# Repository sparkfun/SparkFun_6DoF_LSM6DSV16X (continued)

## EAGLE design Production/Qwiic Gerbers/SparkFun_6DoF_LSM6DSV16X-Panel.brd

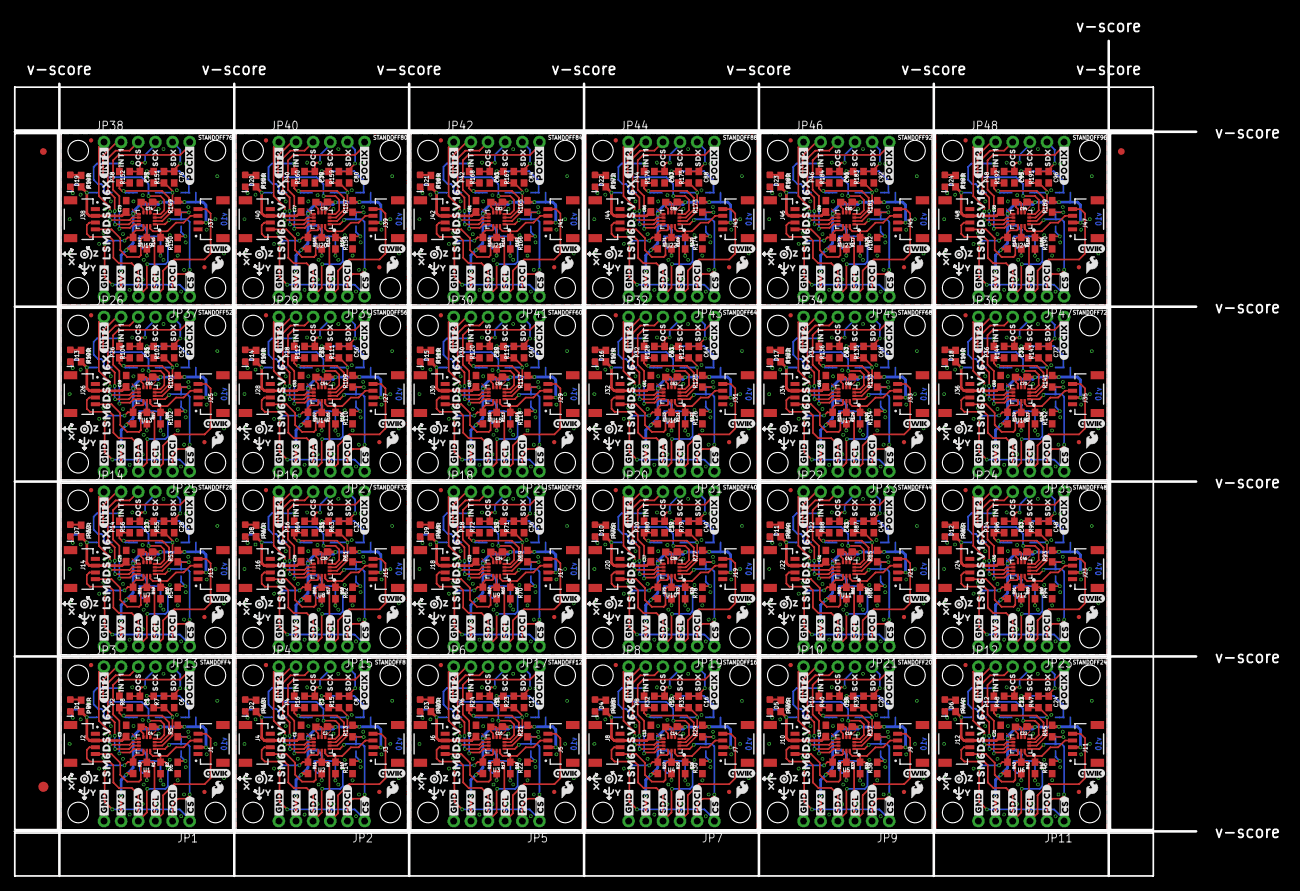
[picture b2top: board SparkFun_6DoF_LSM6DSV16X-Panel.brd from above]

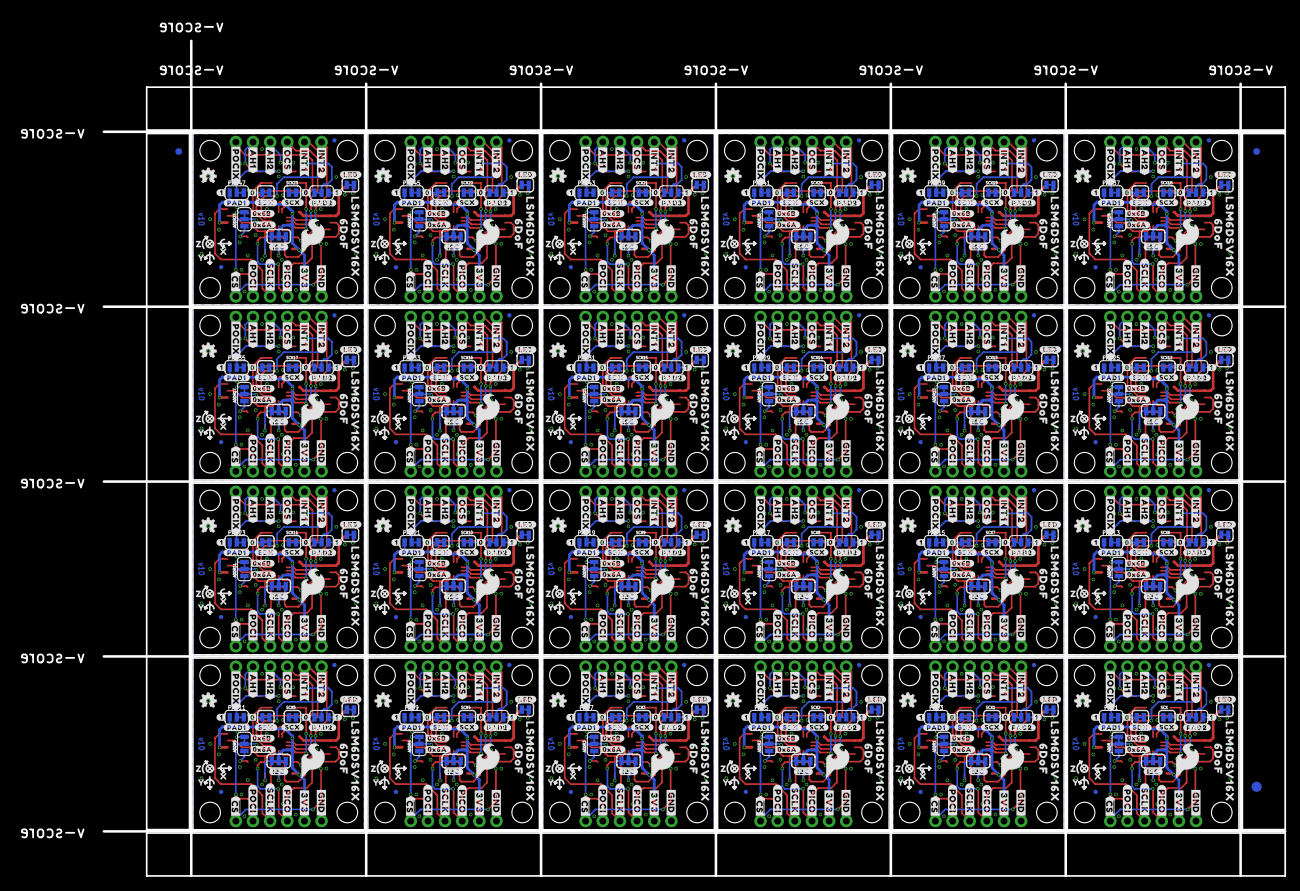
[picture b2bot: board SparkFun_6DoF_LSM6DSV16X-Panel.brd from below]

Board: 2 copper layers, 175.0 x 123.7 mm, 2094 parts (963 on the bottom side), 528 nets.

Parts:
ADDR, ADDR1, ADDR2, ADDR3, ADDR4, ADDR5, ADDR6, ADDR7, ADDR8, ADDR9, ADDR10, ADDR11, ADDR12, ADDR13, ADDR14, ADDR15, ADDR16, ADDR17, ADDR18, ADDR19, ADDR20, ADDR21, ADDR22, ADDR23: JUMPER-SMT_3_1-NC_TRACE_SILK; SMT-JUMPER_3_1-NC_TRACE_SILK
C1, C2, C3, C4, C9, C10, C13, C14, C17, C18, C21, C22, C25, C26, C29, C30, C33, C34, C37, C38, C41, C42, C45, C46, C49, C50, C53, C54, C57, C58, C61, C62, C65, C66, C69, C70, C73, C74, C77, C78, C81, C82, C85, C86, C89, C90, C93, C94: 0.1uF; 0603
C5, C6, C7, C8, C11, C12, C15, C16, C19, C20, C23, C24, C27, C28, C31, C32, C35, C36, C39, C40, C43, C44, C47, C48, C51, C52, C55, C56, C59, C60, C63, C64, C67, C68, C71, C72, C75, C76, C79, C80, C83, C84, C87, C88, C91, C92, C95, C96: 110pF; 0603
D1, D2, D3, D4, D5, D6, D7, D8, D9, D10, D11, D12, D13, D14, D15, D16, D17, D18, D19, D20, D21, D22, D23, D24: RED; LED-0603
E$1, E$2, E$3, E$4: FIDUCIAL-1X2
E$5, E$6: FIDUCIAL-1.5X3
FD1, FD2, FD3, FD4, FD5, FD6, FD7, FD8, FD9, FD10, FD11, FD12, FD13, FD14, FD15, FD16, FD17, FD18, FD19, FD20, FD21, FD22, FD23, FD24, FD25, FD26, FD27, FD28, FD29, FD30, FD31, FD32, FD33, FD34, FD35, FD36, FD37, FD38, FD39, FD40, FD41, FD42, FD43, FD44, FD45, FD46, FD47, FD48: FIDUCIALUFIDUCIAL; FIDUCIAL-MICRO
FID1, FID2, FID3, FID4, FID5, FID6, FID7, FID8, FID9, FID10, FID11, FID12, FID13, FID14, FID15, FID16, FID17, FID18, FID19, FID20, FID21, FID22, FID23, FID24, FID25, FID26, FID27, FID28, FID29, FID30, FID31, FID32, FID33, FID34, FID35, FID36, FID37, FID38, FID39, FID40, FID41, FID42, FID43, FID44, FID45, FID46, FID47, FID48: FIDUCIALUFIDUCIAL; FIDUCIAL-MICRO
FRAME1, FRAME2, FRAME3, FRAME4, FRAME5, FRAME6, FRAME7, FRAME8, FRAME9, FRAME10, FRAME11, FRAME12, FRAME13, FRAME14, FRAME15, FRAME16, FRAME17, FRAME18, FRAME19, FRAME20, FRAME21, FRAME22, FRAME23, FRAME24: FRAME-LEDGER; CREATIVE_COMMONS
I2C_PU, I2C_PU1, I2C_PU2, I2C_PU3, I2C_PU4, I2C_PU5, I2C_PU6, I2C_PU7, I2C_PU8, I2C_PU9, I2C_PU10, I2C_PU11, I2C_PU12, I2C_PU13, I2C_PU14, I2C_PU15, I2C_PU16, I2C_PU17, I2C_PU18, I2C_PU19, I2C_PU20, I2C_PU21, I2C_PU22, I2C_PU23: S_MODE; SMT-JUMPER_3_2-NC_TRACE_SILK
J1, J2, J3, J4, J5, J6, J7, J8, J9, J10, J11, J12, J13, J14, J15, J16, J17, J18, J19, J20, J21, J22, J23, J24, J25, J26, J27, J28, J29, J30, J31, J32, J33, J34, J35, J36, J37, J38, J39, J40, J41, J42, J43, J44, J45, J46, J47, J48: QWIIC_RIGHT_ANGLE; JST04_1MM_RA
JP1, JP2, JP3, JP4, JP5, JP6, JP7, JP8, JP9, JP10, JP11, JP12, JP13, JP14, JP15, JP16, JP17, JP18, JP19, JP20, JP21, JP22, JP23, JP24, JP25, JP26, JP27, JP28, JP29, JP30, JP31, JP32, JP33, JP34, JP35, JP36, JP37, JP38, JP39, JP40, JP41, JP42, JP43, JP44, JP45, JP46, JP47, JP48: IO; 1X06_NO_SILK
LED, LED1, LED2, LED3, LED4, LED5, LED6, LED7, LED8, LED9, LED10, LED11, LED12, LED13, LED14, LED15, LED16, LED17, LED18, LED19, LED20, LED21, LED22, LED23: JUMPER-SMT_2_NC_TRACE_SILK; SMT-JUMPER_2_NC_TRACE_SILK
LOGO1, LOGO5, LOGO8, LOGO11, LOGO14, LOGO17, LOGO20, LOGO23, LOGO26, LOGO29, LOGO32, LOGO35, LOGO38, LOGO41, LOGO44, LOGO47, LOGO50, LOGO53, LOGO56, LOGO59, LOGO62, LOGO65, LOGO68, LOGO71: QWIIC_LOGO_4MM; QWIIC_4MM
LOGO2, LOGO4, LOGO7, LOGO10, LOGO13, LOGO16, LOGO19, LOGO22, LOGO25, LOGO28, LOGO31, LOGO34, LOGO37, LOGO40, LOGO43, LOGO46, LOGO49, LOGO52, LOGO55, LOGO58, LOGO61, LOGO64, LOGO67, LOGO70: OSHW-LOGOMINI; OSHW-LOGO-MINI
LOGO3, LOGO6, LOGO9, LOGO12, LOGO15, LOGO18, LOGO21, LOGO24, LOGO27, LOGO30, LOGO33, LOGO36, LOGO39, LOGO42, LOGO45, LOGO48, LOGO51, LOGO54, LOGO57, LOGO60, LOGO63, LOGO66, LOGO69, LOGO72: SFE_LOGO_NAME_FLAMEBLANK; BLANK
P1, P2, P3, P4, P5, P6, P7, P8, P9, P10, P11, P12, P13, P14, P15, P16, P17, P18, P19, P20, P21, P22, P23, P24, P25, P26, P27, P28, P29, P30, P31, P32, P33, P34, P35, P36, P37, P38, P39, P40, P41, P42, P43, P44, P45, P46, P47, P48: 110pF; 0603
PAD1, PAD2, PAD3, PAD4, PAD5, PAD6, PAD7, PAD8, PAD9, PAD10, PAD11, PAD12, PAD13, PAD14, PAD15, PAD16, PAD17, PAD18, PAD19, PAD20, PAD21, PAD22, PAD23, PAD24, PAD25, PAD26, PAD27, PAD28, PAD29, PAD30, PAD31, PAD32, PAD33, PAD34, PAD35, PAD36, PAD37, PAD38, PAD39, PAD40, PAD41, PAD42, PAD43, PAD44, PAD45, PAD46, PAD47, PAD48: JUMPER-SMT_3_1-NC_TRACE_SILK; SMT-JUMPER_3_1-NC_TRACE_SILK
R1, R2, R9, R10, R17, R18, R25, R26, R33, R34, R41, R42, R49, R50, R57, R58, R65, R66, R73, R74, R81, R82, R89, R90, R97, R98, R105, R106, R113, R114, R121, R122, R129, R130, R137, R138, R145, R146, R153, R154, R161, R162, R169, R170, R177, R178, R185, R186: 2.2k; 0603
R3, R5, R6, R11, R13, R14, R19, R21, R22, R27, R29, R30, R35, R37, R38, R43, R45, R46, R51, R53, R54, R59, R61, R62, R67, R69, R70, R75, R77, R78, R83, R85, R86, R91, R93, R94, R99, R101, R102, R107, R109, R110, R115, R117, R118, R123, R125, R126, R131, R133, R134, R139, R141, R142, R147, R149, R150, R155, R157, R158, R163, R165, R166, R171, R173, R174, R179, R181, R182, R187, R189, R190: 10k; 0603
R4, R12, R20, R28, R36, R44, R52, R60, R68, R76, R84, R92, R100, R108, R116, R124, R132, R140, R148, R156, R164, R172, R180, R188: 4.7k; 0603
R7, R8, R15, R16, R23, R24, R31, R32, R39, R40, R47, R48, R55, R56, R63, R64, R71, R72, R79, R80, R87, R88, R95, R96, R103, R104, R111, R112, R119, R120, R127, R128, R135, R136, R143, R144, R151, R152, R159, R160, R167, R168, R175, R176, R183, R184, R191, R192: 0; 0603
SCX, SCX1, SCX2, SCX3, SCX4, SCX5, SCX6, SCX7, SCX8, SCX9, SCX10, SCX11, SCX12, SCX13, SCX14, SCX15, SCX16, SCX17, SCX18, SCX19, SCX20, SCX21, SCX22, SCX23: JUMPER-SMT_2_NC_TRACE_SILK; SMT-JUMPER_2_NC_TRACE_SILK
SDX, SDX1, SDX2, SDX3, SDX4, SDX5, SDX6, SDX7, SDX8, SDX9, SDX10, SDX11, SDX12, SDX13, SDX14, SDX15, SDX16, SDX17, SDX18, SDX19, SDX20, SDX21, SDX22, SDX23: JUMPER-SMT_2_NC_TRACE_SILK; SMT-JUMPER_2_NC_TRACE_SILK
STANDOFF1, STANDOFF2, STANDOFF3, STANDOFF4, STANDOFF5, STANDOFF6, STANDOFF7, STANDOFF8, STANDOFF9, STANDOFF10, STANDOFF11, STANDOFF12, STANDOFF13, STANDOFF14, STANDOFF15, STANDOFF16, STANDOFF17, STANDOFF18, STANDOFF19, STANDOFF20, STANDOFF21, STANDOFF22, STANDOFF23, STANDOFF24, STANDOFF25, STANDOFF26, STANDOFF27, STANDOFF28, STANDOFF29, STANDOFF30, STANDOFF31, STANDOFF32, STANDOFF33, STANDOFF34, STANDOFF35, STANDOFF36, STANDOFF37, STANDOFF38, STANDOFF39, STANDOFF40, STANDOFF41, STANDOFF42, STANDOFF43, STANDOFF44, STANDOFF45, STANDOFF46, STANDOFF47, STANDOFF48, STANDOFF49, STANDOFF50, STANDOFF51, STANDOFF52, STANDOFF53, STANDOFF54, STANDOFF55, STANDOFF56, STANDOFF57, STANDOFF58, STANDOFF59, STANDOFF60, STANDOFF61, STANDOFF62, STANDOFF63, STANDOFF64, STANDOFF65, STANDOFF66, STANDOFF67, STANDOFF68, STANDOFF69, STANDOFF70, STANDOFF71, STANDOFF72, STANDOFF73, STANDOFF74, STANDOFF75, STANDOFF76, STANDOFF77, STANDOFF78, STANDOFF79, STANDOFF80, STANDOFF81, STANDOFF82, STANDOFF83, STANDOFF84, STANDOFF85, STANDOFF86, STANDOFF87, STANDOFF88, STANDOFF89, STANDOFF90, STANDOFF91, STANDOFF92, STANDOFF93, STANDOFF94, STANDOFF95, STANDOFF96: STAND-OFFTIGHT; STAND-OFF-TIGHT
U1, U2, U3, U4, U5, U6, U7, U8, U9, U10, U11, U12, U13, U14, U15, U16, U17, U18, U19, U20, U21, U22, U23, U24: LSM6DSV16X; LGA-14L
U$1, U$15, U$22, U$53, U$97, U$101, U$145, U$149, U$193, U$197, U$241, U$245, U$289, U$293, U$337, U$341, U$385, U$389, U$433, U$437, U$481, U$485, U$529, U$533, U$577, U$581, U$625, U$629, U$673, U$677, U$721, U$725, U$769, U$773, U$817, U$821, U$865, U$869, U$913, U$917, U$961, U$965, U$1009, U$1013, U$1057, U$1061, U$1105, U$1109: #3V3#1
U$2, U$17, U$50, U$54, U$98, U$102, U$146, U$150, U$194, U$198, U$242, U$246, U$290, U$294, U$338, U$342, U$386, U$390, U$434, U$438, U$482, U$486, U$530, U$534, U$578, U$582, U$626, U$630, U$674, U$678, U$722, U$726, U$770, U$774, U$818, U$822, U$866, U$870, U$914, U$918, U$962, U$966, U$1010, U$1014, U$1058, U$1062, U$1106, U$1110: #GND#0
U$3, U$59, U$107, U$155, U$203, U$251, U$299, U$347, U$395, U$443, U$491, U$539, U$587, U$635, U$683, U$731, U$779, U$827, U$875, U$923, U$971, U$1019, U$1067, U$1115: ##CS##7
U$4, U$51, U$99, U$147, U$195, U$243, U$291, U$339, U$387, U$435, U$483, U$531, U$579, U$627, U$675, U$723, U$771, U$819, U$867, U$915, U$963, U$1011, U$1059, U$1107: #SDA#4
U$5, U$52, U$100, U$148, U$196, U$244, U$292, U$340, U$388, U$436, U$484, U$532, U$580, U$628, U$676, U$724, U$772, U$820, U$868, U$916, U$964, U$1012, U$1060, U$1108: #SCL#5
U$6, U$66, U$114, U$162, U$210, U$258, U$306, U$354, U$402, U$450, U$498, U$546, U$594, U$642, U$690, U$738, U$786, U$834, U$882, U$930, U$978, U$1026, U$1074, U$1122: #POCI#11
U$7, U$76, U$124, U$172, U$220, U$268, U$316, U$364, U$412, U$460, U$508, U$556, U$604, U$652, U$700, U$748, U$796, U$844, U$892, U$940, U$988, U$1036, U$1084, U$1132: INT16
U$8, U$75, U$123, U$171, U$219, U$267, U$315, U$363, U$411, U$459, U$507, U$555, U$603, U$651, U$699, U$747, U$795, U$843, U$891, U$939, U$987, U$1035, U$1083, U$1131: #INT2#2
U$9, U$77, U$125, U$173, U$221, U$269, U$317, U$365, U$413, U$461, U$509, U$557, U$605, U$653, U$701, U$749, U$797, U$845, U$893, U$941, U$989, U$1037, U$1085, U$1133: OCS17
U$10, U$78, U$126, U$174, U$222, U$270, U$318, U$366, U$414, U$462, U$510, U$558, U$606, U$654, U$702, U$750, U$798, U$846, U$894, U$942, U$990, U$1038, U$1086, U$1134: SCX18
U$11, U$79, U$127, U$175, U$223, U$271, U$319, U$367, U$415, U$463, U$511, U$559, U$607, U$655, U$703, U$751, U$799, U$847, U$895, U$943, U$991, U$1039, U$1087, U$1135: SDX19
U$12, U$84, U$132, U$180, U$228, U$276, U$324, U$372, U$420, U$468, U$516, U$564, U$612, U$660, U$708, U$756, U$804, U$852, U$900, U$948, U$996, U$1044, U$1092, U$1140: #AH1#32
U$13, U$55, U$103, U$151, U$199, U$247, U$295, U$343, U$391, U$439, U$487, U$535, U$583, U$631, U$679, U$727, U$775, U$823, U$871, U$919, U$967, U$1015, U$1063, U$1111: #0X6A#11
U$14, U$56, U$104, U$152, U$200, U$248, U$296, U$344, U$392, U$440, U$488, U$536, U$584, U$632, U$680, U$728, U$776, U$824, U$872, U$920, U$968, U$1016, U$1064, U$1112: #0X6B#11
U$16, U$96, U$144, U$192, U$240, U$288, U$336, U$384, U$432, U$480, U$528, U$576, U$624, U$672, U$720, U$768, U$816, U$864, U$912, U$960, U$1008, U$1056, U$1104, U$1152: #LED#4
U$18, U$67, U$115, U$163, U$211, U$259, U$307, U$355, U$403, U$451, U$499, U$547, U$595, U$643, U$691, U$739, U$787, U$835, U$883, U$931, U$979, U$1027, U$1075, U$1123: #POCI#12
U$19, U$85, U$133, U$181, U$229, U$277, U$325, U$373, U$421, U$469, U$517, U$565, U$613, U$661, U$709, U$757, U$805, U$853, U$901, U$949, U$997, U$1045, U$1093, U$1141: #AH2#32
U$20, U$86, U$134, U$182, U$230, U$278, U$326, U$374, U$422, U$470, U$518, U$566, U$614, U$662, U$710, U$758, U$806, U$854, U$902, U$950, U$998, U$1046, U$1094, U$1142: #OCS#32
U$21, U$87, U$135, U$183, U$231, U$279, U$327, U$375, U$423, U$471, U$519, U$567, U$615, U$663, U$711, U$759, U$807, U$855, U$903, U$951, U$999, U$1047, U$1095, U$1143: #INT1#25
U$23, U$93, U$141, U$189, U$237, U$285, U$333, U$381, U$429, U$477, U$525, U$573, U$621, U$669, U$717, U$765, U$813, U$861, U$909, U$957, U$1005, U$1053, U$1101, U$1149: #PAD1#4
U$24, U$63, U$111, U$159, U$207, U$255, U$303, U$351, U$399, U$447, U$495, U$543, U$591, U$639, U$687, U$735, U$783, U$831, U$879, U$927, U$975, U$1023, U$1071, U$1119: #POCIX#8
U$25, U$57, U$105, U$153, U$201, U$249, U$297, U$345, U$393, U$441, U$489, U$537, U$585, U$633, U$681, U$729, U$777, U$825, U$873, U$921, U$969, U$1017, U$1065, U$1113: #I2C#11
U$26, U$65, U$113, U$161, U$209, U$257, U$305, U$353, U$401, U$449, U$497, U$545, U$593, U$641, U$689, U$737, U$785, U$833, U$881, U$929, U$977, U$1025, U$1073, U$1121: #PICO#13
U$27, U$60, U$108, U$156, U$204, U$252, U$300, U$348, U$396, U$444, U$492, U$540, U$588, U$636, U$684, U$732, U$780, U$828, U$876, U$924, U$972, U$1020, U$1068, U$1116: ##CS##8
U$28, U$58, U$106, U$154, U$202, U$250, U$298, U$346, U$394, U$442, U$490, U$538, U$586, U$634, U$682, U$730, U$778, U$826, U$874, U$922, U$970, U$1018, U$1066, U$1114: PWR8
U$29, U$62, U$110, U$158, U$206, U$254, U$302, U$350, U$398, U$446, U$494, U$542, U$590, U$638, U$686, U$734, U$782, U$830, U$878, U$926, U$974, U$1022, U$1070, U$1118: SFE_LOGO_FLAME_.1
U$30, U$94, U$142, U$190, U$238, U$286, U$334, U$382, U$430, U$478, U$526, U$574, U$622, U$670, U$718, U$766, U$814, U$862, U$910, U$958, U$1006, U$1054, U$1102, U$1150: #PAD2#4
U$31, U$61, U$109, U$157, U$205, U$253, U$301, U$349, U$397, U$445, U$493, U$541, U$589, U$637, U$685, U$733, U$781, U$829, U$877, U$925, U$973, U$1021, U$1069, U$1117: 6DOF12
U$32, U$89, U$137, U$185, U$233, U$281, U$329, U$377, U$425, U$473, U$521, U$569, U$617, U$665, U$713, U$761, U$809, U$857, U$905, U$953, U$1001, U$1049, U$1097, U$1145: #1#729
U$33, U$64, U$112, U$160, U$208, U$256, U$304, U$352, U$400, U$448, U$496, U$544, U$592, U$640, U$688, U$736, U$784, U$832, U$880, U$928, U$976, U$1024, U$1072, U$1120: #POCIX#7
U$34, U$37, U$68, U$71, U$116, U$119, U$164, U$167, U$212, U$215, U$260, U$263, U$308, U$311, U$356, U$359, U$404, U$407, U$452, U$455, U$500, U$503, U$548, U$551, U$596, U$599, U$644, U$647, U$692, U$695, U$740, U$743, U$788, U$791, U$836, U$839, U$884, U$887, U$932, U$935, U$980, U$983, U$1028, U$1031, U$1076, U$1079, U$1124, U$1127: X2114
U$35, U$38, U$69, U$72, U$117, U$120, U$165, U$168, U$213, U$216, U$261, U$264, U$309, U$312, U$357, U$360, U$405, U$408, U$453, U$456, U$501, U$504, U$549, U$552, U$597, U$600, U$645, U$648, U$693, U$696, U$741, U$744, U$789, U$792, U$837, U$840, U$885, U$888, U$933, U$936, U$981, U$984, U$1029, U$1032, U$1077, U$1080, U$1125, U$1128: Y2115
U$36, U$39, U$70, U$73, U$118, U$121, U$166, U$169, U$214, U$217, U$262, U$265, U$310, U$313, U$358, U$361, U$406, U$409, U$454, U$457, U$502, U$505, U$550, U$553, U$598, U$601, U$646, U$649, U$694, U$697, U$742, U$745, U$790, U$793, U$838, U$841, U$886, U$889, U$934, U$937, U$982, U$985, U$1030, U$1033, U$1078, U$1081, U$1126, U$1129: Z2116
U$40, U$74, U$122, U$170, U$218, U$266, U$314, U$362, U$410, U$458, U$506, U$554, U$602, U$650, U$698, U$746, U$794, U$842, U$890, U$938, U$986, U$1034, U$1082, U$1130: #INT2#3
U$41, U$88, U$136, U$184, U$232, U$280, U$328, U$376, U$424, U$472, U$520, U$568, U$616, U$664, U$712, U$760, U$808, U$856, U$904, U$952, U$1000, U$1048, U$1096, U$1144: #1#4
U$42, U$80, U$128, U$176, U$224, U$272, U$320, U$368, U$416, U$464, U$512, U$560, U$608, U$656, U$704, U$752, U$800, U$848, U$896, U$944, U$992, U$1040, U$1088, U$1136: #SDX#20
U$43, U$81, U$129, U$177, U$225, U$273, U$321, U$369, U$417, U$465, U$513, U$561, U$609, U$657, U$705, U$753, U$801, U$849, U$897, U$945, U$993, U$1041, U$1089, U$1137: #SCX#19
U$44, U$90, U$138, U$186, U$234, U$282, U$330, U$378, U$426, U$474, U$522, U$570, U$618, U$666, U$714, U$762, U$810, U$858, U$906, U$954, U$1002, U$1050, U$1098, U$1146: SFE_LOGO_FLAME_.2
U$45, U$49, U$91, U$92, U$139, U$140, U$187, U$188, U$235, U$236, U$283, U$284, U$331, U$332, U$379, U$380, U$427, U$428, U$475, U$476, U$523, U$524, U$571, U$572, U$619, U$620, U$667, U$668, U$715, U$716, U$763, U$764, U$811, U$812, U$859, U$860, U$907, U$908, U$955, U$956, U$1003, U$1004, U$1051, U$1052, U$1099, U$1100, U$1147, U$1148: #0#4
U$46, U$47, U$82, U$83, U$130, U$131, U$178, U$179, U$226, U$227, U$274, U$275, U$322, U$323, U$370, U$371, U$418, U$419, U$466, U$467, U$514, U$515, U$562, U$563, U$610, U$611, U$658, U$659, U$706, U$707, U$754, U$755, U$802, U$803, U$850, U$851, U$898, U$899, U$946, U$947, U$994, U$995, U$1042, U$1043, U$1090, U$1091, U$1138, U$1139: LSM6DSV16X37
U$48, U$95, U$143, U$191, U$239, U$287, U$335, U$383, U$431, U$479, U$527, U$575, U$623, U$671, U$719, U$767, U$815, U$863, U$911, U$959, U$1007, U$1055, U$1103, U$1151: #SCLK#4

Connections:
3.3V: C3.1, C4.1, I2C_PU.2, J1.2, J2.2, JP1.5, PAD1.1, PAD2.1, R3.2, R4.2, R5.2, U1.P5, U1.P8
3.3V1: C1.1, C2.1, I2C_PU1.2, J3.2, J4.2, JP2.5, PAD3.1, PAD4.1, R11.2, R12.2, R13.2, U2.P5, U2.P8
3.3V2: C9.1, C10.1, I2C_PU2.2, J5.2, J6.2, JP5.5, PAD5.1, PAD6.1, R19.2, R20.2, R21.2, U3.P5, U3.P8
3.3V3: C13.1, C14.1, I2C_PU3.2, J7.2, J8.2, JP7.5, PAD7.1, PAD8.1, R27.2, R28.2, R29.2, U4.P5, U4.P8
3.3V4: C17.1, C18.1, I2C_PU4.2, J9.2, J10.2, JP9.5, PAD9.1, PAD10.1, R35.2, R36.2, R37.2, U5.P5, U5.P8
3.3V5: C21.1, C22.1, I2C_PU5.2, J11.2, J12.2, JP11.5, PAD11.1, PAD12.1, R43.2, R44.2, R45.2, U6.P5, U6.P8
3.3V6: C25.1, C26.1, I2C_PU6.2, J13.2, J14.2, JP13.5, PAD13.1, PAD14.1, R51.2, R52.2, R53.2, U7.P5, U7.P8
3.3V7: C29.1, C30.1, I2C_PU7.2, J15.2, J16.2, JP15.5, PAD15.1, PAD16.1, R59.2, R60.2, R61.2, U8.P5, U8.P8
3.3V8: C33.1, C34.1, I2C_PU8.2, J17.2, J18.2, JP17.5, PAD17.1, PAD18.1, R67.2, R68.2, R69.2, U9.P5, U9.P8
3.3V9: C37.1, C38.1, I2C_PU9.2, J19.2, J20.2, JP19.5, PAD19.1, PAD20.1, R75.2, R76.2, R77.2, U10.P5, U10.P8
3.3V10: C41.1, C42.1, I2C_PU10.2, J21.2, J22.2, JP21.5, PAD21.1, PAD22.1, R83.2, R84.2, R85.2, U11.P5, U11.P8
3.3V11: C45.1, C46.1, I2C_PU11.2, J23.2, J24.2, JP23.5, PAD23.1, PAD24.1, R91.2, R92.2, R93.2, U12.P5, U12.P8
3.3V12: C49.1, C50.1, I2C_PU12.2, J25.2, J26.2, JP25.5, PAD25.1, PAD26.1, R99.2, R100.2, R101.2, U13.P5, U13.P8
3.3V13: C53.1, C54.1, I2C_PU13.2, J27.2, J28.2, JP27.5, PAD27.1, PAD28.1, R107.2, R108.2, R109.2, U14.P5, U14.P8
3.3V14: C57.1, C58.1, I2C_PU14.2, J29.2, J30.2, JP29.5, PAD29.1, PAD30.1, R115.2, R116.2, R117.2, U15.P5, U15.P8
3.3V15: C61.1, C62.1, I2C_PU15.2, J31.2, J32.2, JP31.5, PAD31.1, PAD32.1, R123.2, R124.2, R125.2, U16.P5, U16.P8
3.3V16: C65.1, C66.1, I2C_PU16.2, J33.2, J34.2, JP33.5, PAD33.1, PAD34.1, R131.2, R132.2, R133.2, U17.P5, U17.P8
3.3V17: C69.1, C70.1, I2C_PU17.2, J35.2, J36.2, JP35.5, PAD35.1, PAD36.1, R139.2, R140.2, R141.2, U18.P5, U18.P8
3.3V18: C73.1, C74.1, I2C_PU18.2, J37.2, J38.2, JP37.5, PAD37.1, PAD38.1, R147.2, R148.2, R149.2, U19.P5, U19.P8
3.3V19: C77.1, C78.1, I2C_PU19.2, J39.2, J40.2, JP39.5, PAD39.1, PAD40.1, R155.2, R156.2, R157.2, U20.P5, U20.P8
3.3V20: C81.1, C82.1, I2C_PU20.2, J41.2, J42.2, JP41.5, PAD41.1, PAD42.1, R163.2, R164.2, R165.2, U21.P5, U21.P8
3.3V21: C85.1, C86.1, I2C_PU21.2, J43.2, J44.2, JP43.5, PAD43.1, PAD44.1, R171.2, R172.2, R173.2, U22.P5, U22.P8
3.3V22: C89.1, C90.1, I2C_PU22.2, J45.2, J46.2, JP45.5, PAD45.1, PAD46.1, R179.2, R180.2, R181.2, U23.P5, U23.P8
3.3V23: C93.1, C94.1, I2C_PU23.2, J47.2, J48.2, JP47.5, PAD47.1, PAD48.1, R187.2, R188.2, R189.2, U24.P5, U24.P8
!CS!: JP1.1, R3.1, U1.P12
!CS!1: JP2.1, R11.1, U2.P12
!CS!2: JP5.1, R19.1, U3.P12
!CS!3: JP7.1, R27.1, U4.P12
!CS!4: JP9.1, R35.1, U5.P12
!CS!5: JP11.1, R43.1, U6.P12
!CS!6: JP13.1, R51.1, U7.P12
!CS!7: JP15.1, R59.1, U8.P12
!CS!8: JP17.1, R67.1, U9.P12
!CS!9: JP19.1, R75.1, U10.P12
!CS!10: JP21.1, R83.1, U11.P12
!CS!11: JP23.1, R91.1, U12.P12
!CS!12: JP25.1, R99.1, U13.P12
!CS!13: JP27.1, R107.1, U14.P12
!CS!14: JP29.1, R115.1, U15.P12
!CS!15: JP31.1, R123.1, U16.P12
!CS!16: JP33.1, R131.1, U17.P12
!CS!17: JP35.1, R139.1, U18.P12
!CS!18: JP37.1, R147.1, U19.P12
!CS!19: JP39.1, R155.1, U20.P12
!CS!20: JP41.1, R163.1, U21.P12
!CS!21: JP43.1, R171.1, U22.P12
!CS!22: JP45.1, R179.1, U23.P12
!CS!23: JP47.1, R187.1, U24.P12
GND: C3.2, C4.2, C5.2, C6.2, J1.1, J2.1, JP1.6, LED.1, PAD1.3, PAD2.3, R6.1, SCX.1, SDX.1, U1.P6, U1.P7
GND1: C1.2, C2.2, C7.2, C8.2, J3.1, J4.1, JP2.6, LED1.1, PAD3.3, PAD4.3, R14.1, SCX1.1, SDX1.1, U2.P6, U2.P7
GND2: C9.2, C10.2, C11.2, C12.2, J5.1, J6.1, JP5.6, LED2.1, PAD5.3, PAD6.3, R22.1, SCX2.1, SDX2.1, U3.P6, U3.P7
GND3: C13.2, C14.2, C15.2, C16.2, J7.1, J8.1, JP7.6, LED3.1, PAD7.3, PAD8.3, R30.1, SCX3.1, SDX3.1, U4.P6, U4.P7
GND4: C17.2, C18.2, C19.2, C20.2, J9.1, J10.1, JP9.6, LED4.1, PAD9.3, PAD10.3, R38.1, SCX4.1, SDX4.1, U5.P6, U5.P7
GND5: C21.2, C22.2, C23.2, C24.2, J11.1, J12.1, JP11.6, LED5.1, PAD11.3, PAD12.3, R46.1, SCX5.1, SDX5.1, U6.P6, U6.P7
GND6: C25.2, C26.2, C27.2, C28.2, J13.1, J14.1, JP13.6, LED6.1, PAD13.3, PAD14.3, R54.1, SCX6.1, SDX6.1, U7.P6, U7.P7
GND7: C29.2, C30.2, C31.2, C32.2, J15.1, J16.1, JP15.6, LED7.1, PAD15.3, PAD16.3, R62.1, SCX7.1, SDX7.1, U8.P6, U8.P7
GND8: C33.2, C34.2, C35.2, C36.2, J17.1, J18.1, JP17.6, LED8.1, PAD17.3, PAD18.3, R70.1, SCX8.1, SDX8.1, U9.P6, U9.P7
GND9: C37.2, C38.2, C39.2, C40.2, J19.1, J20.1, JP19.6, LED9.1, PAD19.3, PAD20.3, R78.1, SCX9.1, SDX9.1, U10.P6, U10.P7
GND10: C41.2, C42.2, C43.2, C44.2, J21.1, J22.1, JP21.6, LED10.1, PAD21.3, PAD22.3, R86.1, SCX10.1, SDX10.1, U11.P6, U11.P7
GND11: C45.2, C46.2, C47.2, C48.2, J23.1, J24.1, JP23.6, LED11.1, PAD23.3, PAD24.3, R94.1, SCX11.1, SDX11.1, U12.P6, U12.P7
GND12: C49.2, C50.2, C51.2, C52.2, J25.1, J26.1, JP25.6, LED12.1, PAD25.3, PAD26.3, R102.1, SCX12.1, SDX12.1, U13.P6, U13.P7
GND13: C53.2, C54.2, C55.2, C56.2, J27.1, J28.1, JP27.6, LED13.1, PAD27.3, PAD28.3, R110.1, SCX13.1, SDX13.1, U14.P6, U14.P7
GND14: C57.2, C58.2, C59.2, C60.2, J29.1, J30.1, JP29.6, LED14.1, PAD29.3, PAD30.3, R118.1, SCX14.1, SDX14.1, U15.P6, U15.P7
GND15: C61.2, C62.2, C63.2, C64.2, J31.1, J32.1, JP31.6, LED15.1, PAD31.3, PAD32.3, R126.1, SCX15.1, SDX15.1, U16.P6, U16.P7
GND16: C65.2, C66.2, C67.2, C68.2, J33.1, J34.1, JP33.6, LED16.1, PAD33.3, PAD34.3, R134.1, SCX16.1, SDX16.1, U17.P6, U17.P7
GND17: C69.2, C70.2, C71.2, C72.2, J35.1, J36.1, JP35.6, LED17.1, PAD35.3, PAD36.3, R142.1, SCX17.1, SDX17.1, U18.P6, U18.P7
GND18: C73.2, C74.2, C75.2, C76.2, J37.1, J38.1, JP37.6, LED18.1, PAD37.3, PAD38.3, R150.1, SCX18.1, SDX18.1, U19.P6, U19.P7
GND19: C77.2, C78.2, C79.2, C80.2, J39.1, J40.1, JP39.6, LED19.1, PAD39.3, PAD40.3, R158.1, SCX19.1, SDX19.1, U20.P6, U20.P7
GND20: C81.2, C82.2, C83.2, C84.2, J41.1, J42.1, JP41.6, LED20.1, PAD41.3, PAD42.3, R166.1, SCX20.1, SDX20.1, U21.P6, U21.P7
GND21: C85.2, C86.2, C87.2, C88.2, J43.1, J44.1, JP43.6, LED21.1, PAD43.3, PAD44.3, R174.1, SCX21.1, SDX21.1, U22.P6, U22.P7
GND22: C89.2, C90.2, C91.2, C92.2, J45.1, J46.1, JP45.6, LED22.1, PAD45.3, PAD46.3, R182.1, SCX22.1, SDX22.1, U23.P6, U23.P7
GND23: C93.2, C94.2, C95.2, C96.2, J47.1, J48.1, JP47.6, LED23.1, PAD47.3, PAD48.3, R190.1, SCX23.1, SDX23.1, U24.P6, U24.P7
INT1: JP3.2, U1.P4
INT2: JP3.1, U1.P9
INT3: JP4.2, U2.P4
INT4: JP4.1, U2.P9
INT5: JP6.2, U3.P4
INT6: JP6.1, U3.P9
INT7: JP8.2, U4.P4
INT8: JP8.1, U4.P9
INT9: JP10.2, U5.P4
INT10: JP10.1, U5.P9
INT11: JP12.2, U6.P4
INT12: JP12.1, U6.P9
INT13: JP14.2, U7.P4
INT14: JP14.1, U7.P9
INT15: JP16.2, U8.P4
INT16: JP16.1, U8.P9
INT17: JP18.2, U9.P4
INT18: JP18.1, U9.P9
INT19: JP20.2, U10.P4
INT20: JP20.1, U10.P9
INT21: JP22.2, U11.P4
INT22: JP22.1, U11.P9
INT23: JP24.2, U12.P4
INT24: JP24.1, U12.P9
INT25: JP26.2, U13.P4
INT26: JP26.1, U13.P9
INT27: JP28.2, U14.P4
INT28: JP28.1, U14.P9
INT29: JP30.2, U15.P4
INT30: JP30.1, U15.P9
INT31: JP32.2, U16.P4
INT32: JP32.1, U16.P9
INT33: JP34.2, U17.P4
INT34: JP34.1, U17.P9
INT35: JP36.2, U18.P4
INT36: JP36.1, U18.P9
INT37: JP38.2, U19.P4
INT38: JP38.1, U19.P9
INT39: JP40.2, U20.P4
INT40: JP40.1, U20.P9
INT41: JP42.2, U21.P4
INT42: JP42.1, U21.P9
INT43: JP44.2, U22.P4
INT44: JP44.1, U22.P9
INT45: JP46.2, U23.P4
INT46: JP46.1, U23.P9
INT47: JP48.2, U24.P4
INT48: JP48.1, U24.P9
unnamed: ADDR.3, R5.1
unnamed: D1.A, R4.1
unnamed: D1.C, LED.2
unnamed: P2.2, PAD2.2
unnamed: I2C_PU.1, R1.2
unnamed: I2C_PU.3, R2.2
unnamed: ADDR.1, R6.2
unnamed: P1.2, PAD1.2
unnamed: I2C_PU1.1, R9.2
unnamed: I2C_PU1.3, R10.2
unnamed: D2.A, R12.1
unnamed: D2.C, LED1.2
unnamed: ADDR1.3, R13.1
unnamed: ADDR1.1, R14.2
unnamed: P3.2, PAD3.2
unnamed: P4.2, PAD4.2
unnamed: I2C_PU2.1, R17.2
unnamed: I2C_PU2.3, R18.2
unnamed: D3.A, R20.1
unnamed: D3.C, LED2.2
unnamed: ADDR2.3, R21.1
unnamed: ADDR2.1, R22.2
unnamed: P5.2, PAD5.2
unnamed: P6.2, PAD6.2
unnamed: I2C_PU3.1, R25.2
unnamed: I2C_PU3.3, R26.2
unnamed: D4.A, R28.1
unnamed: D4.C, LED3.2
unnamed: ADDR3.3, R29.1
unnamed: ADDR3.1, R30.2
unnamed: P7.2, PAD7.2
unnamed: P8.2, PAD8.2
unnamed: I2C_PU4.1, R33.2
unnamed: I2C_PU4.3, R34.2
unnamed: D5.A, R36.1
unnamed: D5.C, LED4.2
unnamed: ADDR4.3, R37.1
unnamed: ADDR4.1, R38.2
unnamed: P9.2, PAD9.2
unnamed: P10.2, PAD10.2
unnamed: I2C_PU5.1, R41.2
unnamed: I2C_PU5.3, R42.2
unnamed: D6.A, R44.1
unnamed: D6.C, LED5.2
unnamed: ADDR5.3, R45.1
unnamed: ADDR5.1, R46.2
unnamed: P11.2, PAD11.2
unnamed: P12.2, PAD12.2
unnamed: I2C_PU6.1, R49.2
unnamed: I2C_PU6.3, R50.2
unnamed: D7.A, R52.1
unnamed: D7.C, LED6.2
unnamed: ADDR6.3, R53.1
unnamed: ADDR6.1, R54.2
unnamed: P13.2, PAD13.2
unnamed: P14.2, PAD14.2
unnamed: I2C_PU7.1, R57.2
unnamed: I2C_PU7.3, R58.2
unnamed: D8.A, R60.1
unnamed: D8.C, LED7.2
unnamed: ADDR7.3, R61.1
unnamed: ADDR7.1, R62.2
unnamed: P15.2, PAD15.2
unnamed: P16.2, PAD16.2
unnamed: I2C_PU8.1, R65.2
unnamed: I2C_PU8.3, R66.2
unnamed: D9.A, R68.1
unnamed: D9.C, LED8.2
unnamed: ADDR8.3, R69.1
unnamed: ADDR8.1, R70.2
unnamed: P17.2, PAD17.2
unnamed: P18.2, PAD18.2
unnamed: I2C_PU9.1, R73.2
unnamed: I2C_PU9.3, R74.2
unnamed: D10.A, R76.1
unnamed: D10.C, LED9.2
unnamed: ADDR9.3, R77.1
unnamed: ADDR9.1, R78.2
unnamed: P19.2, PAD19.2
unnamed: P20.2, PAD20.2
unnamed: I2C_PU10.1, R81.2
unnamed: I2C_PU10.3, R82.2
unnamed: D11.A, R84.1
unnamed: D11.C, LED10.2
unnamed: ADDR10.3, R85.1
unnamed: ADDR10.1, R86.2
unnamed: P21.2, PAD21.2
unnamed: P22.2, PAD22.2
unnamed: I2C_PU11.1, R89.2
unnamed: I2C_PU11.3, R90.2
unnamed: D12.A, R92.1
unnamed: D12.C, LED11.2
unnamed: ADDR11.3, R93.1
unnamed: ADDR11.1, R94.2
unnamed: P23.2, PAD23.2
unnamed: P24.2, PAD24.2
unnamed: I2C_PU12.1, R97.2
unnamed: I2C_PU12.3, R98.2
unnamed: D13.A, R100.1
unnamed: D13.C, LED12.2
unnamed: ADDR12.3, R101.1
unnamed: ADDR12.1, R102.2
unnamed: P25.2, PAD25.2
unnamed: P26.2, PAD26.2
unnamed: I2C_PU13.1, R105.2
unnamed: I2C_PU13.3, R106.2
unnamed: D14.A, R108.1
unnamed: D14.C, LED13.2
unnamed: ADDR13.3, R109.1
unnamed: ADDR13.1, R110.2
unnamed: P27.2, PAD27.2
unnamed: P28.2, PAD28.2
unnamed: I2C_PU14.1, R113.2
unnamed: I2C_PU14.3, R114.2
unnamed: D15.A, R116.1
unnamed: D15.C, LED14.2
unnamed: ADDR14.3, R117.1
unnamed: ADDR14.1, R118.2
unnamed: P29.2, PAD29.2
unnamed: P30.2, PAD30.2
unnamed: I2C_PU15.1, R121.2
unnamed: I2C_PU15.3, R122.2
unnamed: D16.A, R124.1
unnamed: D16.C, LED15.2
unnamed: ADDR15.3, R125.1
unnamed: ADDR15.1, R126.2
unnamed: P31.2, PAD31.2
unnamed: P32.2, PAD32.2
unnamed: I2C_PU16.1, R129.2
unnamed: I2C_PU16.3, R130.2
unnamed: D17.A, R132.1
unnamed: D17.C, LED16.2
unnamed: ADDR16.3, R133.1
unnamed: ADDR16.1, R134.2
unnamed: P33.2, PAD33.2
unnamed: P34.2, PAD34.2
unnamed: I2C_PU17.1, R137.2
unnamed: I2C_PU17.3, R138.2
unnamed: D18.A, R140.1
unnamed: D18.C, LED17.2
unnamed: ADDR17.3, R141.1
unnamed: ADDR17.1, R142.2
unnamed: P35.2, PAD35.2
unnamed: P36.2, PAD36.2
unnamed: I2C_PU18.1, R145.2
unnamed: I2C_PU18.3, R146.2
unnamed: D19.A, R148.1
unnamed: D19.C, LED18.2
unnamed: ADDR18.3, R149.1
unnamed: ADDR18.1, R150.2
unnamed: P37.2, PAD37.2
unnamed: P38.2, PAD38.2
unnamed: I2C_PU19.1, R153.2
unnamed: I2C_PU19.3, R154.2
unnamed: D20.A, R156.1
unnamed: D20.C, LED19.2
unnamed: ADDR19.3, R157.1
unnamed: ADDR19.1, R158.2
unnamed: P39.2, PAD39.2
unnamed: P40.2, PAD40.2
unnamed: I2C_PU20.1, R161.2
unnamed: I2C_PU20.3, R162.2
unnamed: D21.A, R164.1
unnamed: D21.C, LED20.2
unnamed: ADDR20.3, R165.1
unnamed: ADDR20.1, R166.2
unnamed: P41.2, PAD41.2
unnamed: P42.2, PAD42.2
unnamed: I2C_PU21.1, R169.2
unnamed: I2C_PU21.3, R170.2
unnamed: D22.A, R172.1
unnamed: D22.C, LED21.2
unnamed: ADDR21.3, R173.1
unnamed: ADDR21.1, R174.2
unnamed: P43.2, PAD43.2
unnamed: P44.2, PAD44.2
unnamed: I2C_PU22.1, R177.2
unnamed: I2C_PU22.3, R178.2
unnamed: D23.A, R180.1
unnamed: D23.C, LED22.2
unnamed: ADDR22.3, R181.1
unnamed: ADDR22.1, R182.2
unnamed: P45.2, PAD45.2
unnamed: P46.2, PAD46.2
unnamed: I2C_PU23.1, R185.2
unnamed: I2C_PU23.3, R186.2
unnamed: D24.A, R188.1
unnamed: D24.C, LED23.2
unnamed: ADDR23.3, R189.1
unnamed: ADDR23.1, R190.2
unnamed: P47.2, PAD47.2
unnamed: P48.2, PAD48.2
OCS: JP3.3, U1.P10
OCS1: JP4.3, U2.P10
OCS2: JP6.3, U3.P10
OCS3: JP8.3, U4.P10
OCS4: JP10.3, U5.P10
OCS5: JP12.3, U6.P10
OCS6: JP14.3, U7.P10
OCS7: JP16.3, U8.P10
OCS8: JP18.3, U9.P10
OCS9: JP20.3, U10.P10
OCS10: JP22.3, U11.P10
OCS11: JP24.3, U12.P10
OCS12: JP26.3, U13.P10
OCS13: JP28.3, U14.P10
OCS14: JP30.3, U15.P10
OCS15: JP32.3, U16.P10
OCS16: JP34.3, U17.P10
OCS17: JP36.3, U18.P10
OCS18: JP38.3, U19.P10
OCS19: JP40.3, U20.P10
OCS20: JP42.3, U21.P10
OCS21: JP44.3, U22.P10
OCS22: JP46.3, U23.P10
OCS23: JP48.3, U24.P10
POCI/SA0: ADDR.2, JP1.2, U1.P1
POCI/SA1: ADDR1.2, JP2.2, U2.P1
POCI/SA2: ADDR2.2, JP5.2, U3.P1
POCI/SA3: ADDR3.2, JP7.2, U4.P1
POCI/SA4: ADDR4.2, JP9.2, U5.P1
POCI/SA5: ADDR5.2, JP11.2, U6.P1
POCI/SA6: ADDR6.2, JP13.2, U7.P1
POCI/SA7: ADDR7.2, JP15.2, U8.P1
POCI/SA8: ADDR8.2, JP17.2, U9.P1
POCI/SA9: ADDR9.2, JP19.2, U10.P1
POCI/SA10: ADDR10.2, JP21.2, U11.P1
POCI/SA11: ADDR11.2, JP23.2, U12.P1
POCI/SA12: ADDR12.2, JP25.2, U13.P1
POCI/SA13: ADDR13.2, JP27.2, U14.P1
POCI/SA14: ADDR14.2, JP29.2, U15.P1
POCI/SA15: ADDR15.2, JP31.2, U16.P1
POCI/SA16: ADDR16.2, JP33.2, U17.P1
POCI/SA17: ADDR17.2, JP35.2, U18.P1
POCI/SA18: ADDR18.2, JP37.2, U19.P1
POCI/SA19: ADDR19.2, JP39.2, U20.P1
POCI/SA20: ADDR20.2, JP41.2, U21.P1
POCI/SA21: ADDR21.2, JP43.2, U22.P1
POCI/SA22: ADDR22.2, JP45.2, U23.P1
POCI/SA23: ADDR23.2, JP47.2, U24.P1
POCI_AUX: JP3.6, U1.P11
POCI_AUX1: JP4.6, U2.P11
POCI_AUX2: JP6.6, U3.P11
POCI_AUX3: JP8.6, U4.P11
POCI_AUX4: JP10.6, U5.P11
POCI_AUX5: JP12.6, U6.P11
POCI_AUX6: JP14.6, U7.P11
POCI_AUX7: JP16.6, U8.P11
POCI_AUX8: JP18.6, U9.P11
POCI_AUX9: JP20.6, U10.P11
POCI_AUX10: JP22.6, U11.P11
POCI_AUX11: JP24.6, U12.P11
POCI_AUX12: JP26.6, U13.P11
POCI_AUX13: JP28.6, U14.P11
POCI_AUX14: JP30.6, U15.P11
POCI_AUX15: JP32.6, U16.P11
POCI_AUX16: JP34.6, U17.P11
POCI_AUX17: JP36.6, U18.P11
POCI_AUX18: JP38.6, U19.P11
POCI_AUX19: JP40.6, U20.P11
POCI_AUX20: JP42.6, U21.P11
POCI_AUX21: JP44.6, U22.P11
POCI_AUX22: JP46.6, U23.P11
POCI_AUX23: JP48.6, U24.P11
SCL/SCLK: J1.4, J2.4, JP1.3, R1.1, U1.P13
SCL/SCLK1: J3.4, J4.4, JP2.3, R9.1, U2.P13
SCL/SCLK2: J5.4, J6.4, JP5.3, R17.1, U3.P13
SCL/SCLK3: J7.4, J8.4, JP7.3, R25.1, U4.P13
SCL/SCLK4: J9.4, J10.4, JP9.3, R33.1, U5.P13
SCL/SCLK5: J11.4, J12.4, JP11.3, R41.1, U6.P13
SCL/SCLK6: J13.4, J14.4, JP13.3, R49.1, U7.P13
SCL/SCLK7: J15.4, J16.4, JP15.3, R57.1, U8.P13
SCL/SCLK8: J17.4, J18.4, JP17.3, R65.1, U9.P13
SCL/SCLK9: J19.4, J20.4, JP19.3, R73.1, U10.P13
SCL/SCLK10: J21.4, J22.4, JP21.3, R81.1, U11.P13
SCL/SCLK11: J23.4, J24.4, JP23.3, R89.1, U12.P13
SCL/SCLK12: J25.4, J26.4, JP25.3, R97.1, U13.P13
SCL/SCLK13: J27.4, J28.4, JP27.3, R105.1, U14.P13
SCL/SCLK14: J29.4, J30.4, JP29.3, R113.1, U15.P13
SCL/SCLK15: J31.4, J32.4, JP31.3, R121.1, U16.P13
SCL/SCLK16: J33.4, J34.4, JP33.3, R129.1, U17.P13
SCL/SCLK17: J35.4, J36.4, JP35.3, R137.1, U18.P13
SCL/SCLK18: J37.4, J38.4, JP37.3, R145.1, U19.P13
SCL/SCLK19: J39.4, J40.4, JP39.3, R153.1, U20.P13
SCL/SCLK20: J41.4, J42.4, JP41.3, R161.1, U21.P13
SCL/SCLK21: J43.4, J44.4, JP43.3, R169.1, U22.P13
SCL/SCLK22: J45.4, J46.4, JP45.3, R177.1, U23.P13
SCL/SCLK23: J47.4, J48.4, JP47.3, R185.1, U24.P13
SCX/AH2/QVAR1: C7.1, JP4.4, R16.2
SCX/AH2/QVAR2: C5.1, JP3.4, R8.2
SCX/AH2/QVAR2_FILTER: P2.1, R8.1, SCX.2, U1.P3
SCX/AH2/QVAR2_FILTER1: P4.1, R16.1, SCX1.2, U2.P3
SCX/AH2/QVAR2_FILTER2: P6.1, R24.1, SCX2.2, U3.P3
SCX/AH2/QVAR2_FILTER3: P8.1, R32.1, SCX3.2, U4.P3
SCX/AH2/QVAR2_FILTER4: P10.1, R40.1, SCX4.2, U5.P3
SCX/AH2/QVAR2_FILTER5: P12.1, R48.1, SCX5.2, U6.P3
SCX/AH2/QVAR2_FILTER6: P14.1, R56.1, SCX6.2, U7.P3
SCX/AH2/QVAR2_FILTER7: P16.1, R64.1, SCX7.2, U8.P3
SCX/AH2/QVAR2_FILTER8: P18.1, R72.1, SCX8.2, U9.P3
SCX/AH2/QVAR2_FILTER9: P20.1, R80.1, SCX9.2, U10.P3
SCX/AH2/QVAR2_FILTER10: P22.1, R88.1, SCX10.2, U11.P3
SCX/AH2/QVAR2_FILTER11: P24.1, R96.1, SCX11.2, U12.P3
SCX/AH2/QVAR2_FILTER12: P26.1, R104.1, SCX12.2, U13.P3
SCX/AH2/QVAR2_FILTER13: P28.1, R112.1, SCX13.2, U14.P3
SCX/AH2/QVAR2_FILTER14: P30.1, R120.1, SCX14.2, U15.P3
SCX/AH2/QVAR2_FILTER15: P32.1, R128.1, SCX15.2, U16.P3
SCX/AH2/QVAR2_FILTER16: P34.1, R136.1, SCX16.2, U17.P3
SCX/AH2/QVAR2_FILTER17: P36.1, R144.1, SCX17.2, U18.P3
SCX/AH2/QVAR2_FILTER18: P38.1, R152.1, SCX18.2, U19.P3
SCX/AH2/QVAR2_FILTER19: P40.1, R160.1, SCX19.2, U20.P3
SCX/AH2/QVAR2_FILTER20: P42.1, R168.1, SCX20.2, U21.P3
SCX/AH2/QVAR2_FILTER21: P44.1, R176.1, SCX21.2, U22.P3
SCX/AH2/QVAR2_FILTER22: P46.1, R184.1, SCX22.2, U23.P3
SCX/AH2/QVAR2_FILTER23: P48.1, R192.1, SCX23.2, U24.P3
SCX/AH2/QVAR3: C11.1, JP6.4, R24.2
SCX/AH2/QVAR4: C15.1, JP8.4, R32.2
SCX/AH2/QVAR5: C19.1, JP10.4, R40.2
SCX/AH2/QVAR6: C23.1, JP12.4, R48.2
SCX/AH2/QVAR7: C27.1, JP14.4, R56.2
SCX/AH2/QVAR8: C31.1, JP16.4, R64.2
SCX/AH2/QVAR9: C35.1, JP18.4, R72.2
SCX/AH2/QVAR10: C39.1, JP20.4, R80.2
SCX/AH2/QVAR11: C43.1, JP22.4, R88.2
SCX/AH2/QVAR12: C47.1, JP24.4, R96.2
SCX/AH2/QVAR13: C51.1, JP26.4, R104.2
SCX/AH2/QVAR14: C55.1, JP28.4, R112.2
SCX/AH2/QVAR15: C59.1, JP30.4, R120.2
SCX/AH2/QVAR16: C63.1, JP32.4, R128.2
SCX/AH2/QVAR17: C67.1, JP34.4, R136.2
SCX/AH2/QVAR18: C71.1, JP36.4, R144.2
SCX/AH2/QVAR19: C75.1, JP38.4, R152.2
SCX/AH2/QVAR20: C79.1, JP40.4, R160.2
SCX/AH2/QVAR21: C83.1, JP42.4, R168.2
SCX/AH2/QVAR22: C87.1, JP44.4, R176.2
SCX/AH2/QVAR23: C91.1, JP46.4, R184.2
SCX/AH2/QVAR24: C95.1, JP48.4, R192.2
SDA/PICO: J1.3, J2.3, JP1.4, R2.1, U1.P14
SDA/PICO1: J3.3, J4.3, JP2.4, R10.1, U2.P14
SDA/PICO2: J5.3, J6.3, JP5.4, R18.1, U3.P14
SDA/PICO3: J7.3, J8.3, JP7.4, R26.1, U4.P14
SDA/PICO4: J9.3, J10.3, JP9.4, R34.1, U5.P14
SDA/PICO5: J11.3, J12.3, JP11.4, R42.1, U6.P14
SDA/PICO6: J13.3, J14.3, JP13.4, R50.1, U7.P14
SDA/PICO7: J15.3, J16.3, JP15.4, R58.1, U8.P14
SDA/PICO8: J17.3, J18.3, JP17.4, R66.1, U9.P14
SDA/PICO9: J19.3, J20.3, JP19.4, R74.1, U10.P14
SDA/PICO10: J21.3, J22.3, JP21.4, R82.1, U11.P14
SDA/PICO11: J23.3, J24.3, JP23.4, R90.1, U12.P14
SDA/PICO12: J25.3, J26.3, JP25.4, R98.1, U13.P14
SDA/PICO13: J27.3, J28.3, JP27.4, R106.1, U14.P14
SDA/PICO14: J29.3, J30.3, JP29.4, R114.1, U15.P14
SDA/PICO15: J31.3, J32.3, JP31.4, R122.1, U16.P14
SDA/PICO16: J33.3, J34.3, JP33.4, R130.1, U17.P14
SDA/PICO17: J35.3, J36.3, JP35.4, R138.1, U18.P14
SDA/PICO18: J37.3, J38.3, JP37.4, R146.1, U19.P14
SDA/PICO19: J39.3, J40.3, JP39.4, R154.1, U20.P14
SDA/PICO20: J41.3, J42.3, JP41.4, R162.1, U21.P14
SDA/PICO21: J43.3, J44.3, JP43.4, R170.1, U22.P14
SDA/PICO22: J45.3, J46.3, JP45.4, R178.1, U23.P14
SDA/PICO23: J47.3, J48.3, JP47.4, R186.1, U24.P14
SDX/AH1/QVAR1: C6.1, JP3.5, R7.2
SDX/AH1/QVAR1_FILTER: P1.1, R7.1, SDX.2, U1.P2
SDX/AH1/QVAR1_FILTER1: P3.1, R15.1, SDX1.2, U2.P2
SDX/AH1/QVAR1_FILTER2: P5.1, R23.1, SDX2.2, U3.P2
SDX/AH1/QVAR1_FILTER3: P7.1, R31.1, SDX3.2, U4.P2
SDX/AH1/QVAR1_FILTER4: P9.1, R39.1, SDX4.2, U5.P2
SDX/AH1/QVAR1_FILTER5: P11.1, R47.1, SDX5.2, U6.P2
SDX/AH1/QVAR1_FILTER6: P13.1, R55.1, SDX6.2, U7.P2
SDX/AH1/QVAR1_FILTER7: P15.1, R63.1, SDX7.2, U8.P2
SDX/AH1/QVAR1_FILTER8: P17.1, R71.1, SDX8.2, U9.P2
SDX/AH1/QVAR1_FILTER9: P19.1, R79.1, SDX9.2, U10.P2
SDX/AH1/QVAR1_FILTER10: P21.1, R87.1, SDX10.2, U11.P2
SDX/AH1/QVAR1_FILTER11: P23.1, R95.1, SDX11.2, U12.P2
SDX/AH1/QVAR1_FILTER12: P25.1, R103.1, SDX12.2, U13.P2
SDX/AH1/QVAR1_FILTER13: P27.1, R111.1, SDX13.2, U14.P2
SDX/AH1/QVAR1_FILTER14: P29.1, R119.1, SDX14.2, U15.P2
SDX/AH1/QVAR1_FILTER15: P31.1, R127.1, SDX15.2, U16.P2
SDX/AH1/QVAR1_FILTER16: P33.1, R135.1, SDX16.2, U17.P2
SDX/AH1/QVAR1_FILTER17: P35.1, R143.1, SDX17.2, U18.P2
SDX/AH1/QVAR1_FILTER18: P37.1, R151.1, SDX18.2, U19.P2
SDX/AH1/QVAR1_FILTER19: P39.1, R159.1, SDX19.2, U20.P2
SDX/AH1/QVAR1_FILTER20: P41.1, R167.1, SDX20.2, U21.P2
SDX/AH1/QVAR1_FILTER21: P43.1, R175.1, SDX21.2, U22.P2
SDX/AH1/QVAR1_FILTER22: P45.1, R183.1, SDX22.2, U23.P2
SDX/AH1/QVAR1_FILTER23: P47.1, R191.1, SDX23.2, U24.P2
SDX/AH1/QVAR2: C8.1, JP4.5, R15.2
SDX/AH1/QVAR3: C12.1, JP6.5, R23.2
SDX/AH1/QVAR4: C16.1, JP8.5, R31.2
SDX/AH1/QVAR5: C20.1, JP10.5, R39.2
SDX/AH1/QVAR6: C24.1, JP12.5, R47.2
SDX/AH1/QVAR7: C28.1, JP14.5, R55.2
SDX/AH1/QVAR8: C32.1, JP16.5, R63.2
SDX/AH1/QVAR9: C36.1, JP18.5, R71.2
SDX/AH1/QVAR10: C40.1, JP20.5, R79.2
SDX/AH1/QVAR11: C44.1, JP22.5, R87.2
SDX/AH1/QVAR12: C48.1, JP24.5, R95.2
SDX/AH1/QVAR13: C52.1, JP26.5, R103.2
SDX/AH1/QVAR14: C56.1, JP28.5, R111.2
SDX/AH1/QVAR15: C60.1, JP30.5, R119.2
SDX/AH1/QVAR16: C64.1, JP32.5, R127.2
SDX/AH1/QVAR17: C68.1, JP34.5, R135.2
SDX/AH1/QVAR18: C72.1, JP36.5, R143.2
SDX/AH1/QVAR19: C76.1, JP38.5, R151.2
SDX/AH1/QVAR20: C80.1, JP40.5, R159.2
SDX/AH1/QVAR21: C84.1, JP42.5, R167.2
SDX/AH1/QVAR22: C88.1, JP44.5, R175.2
SDX/AH1/QVAR23: C92.1, JP46.5, R183.2
SDX/AH1/QVAR24: C96.1, JP48.5, R191.2
